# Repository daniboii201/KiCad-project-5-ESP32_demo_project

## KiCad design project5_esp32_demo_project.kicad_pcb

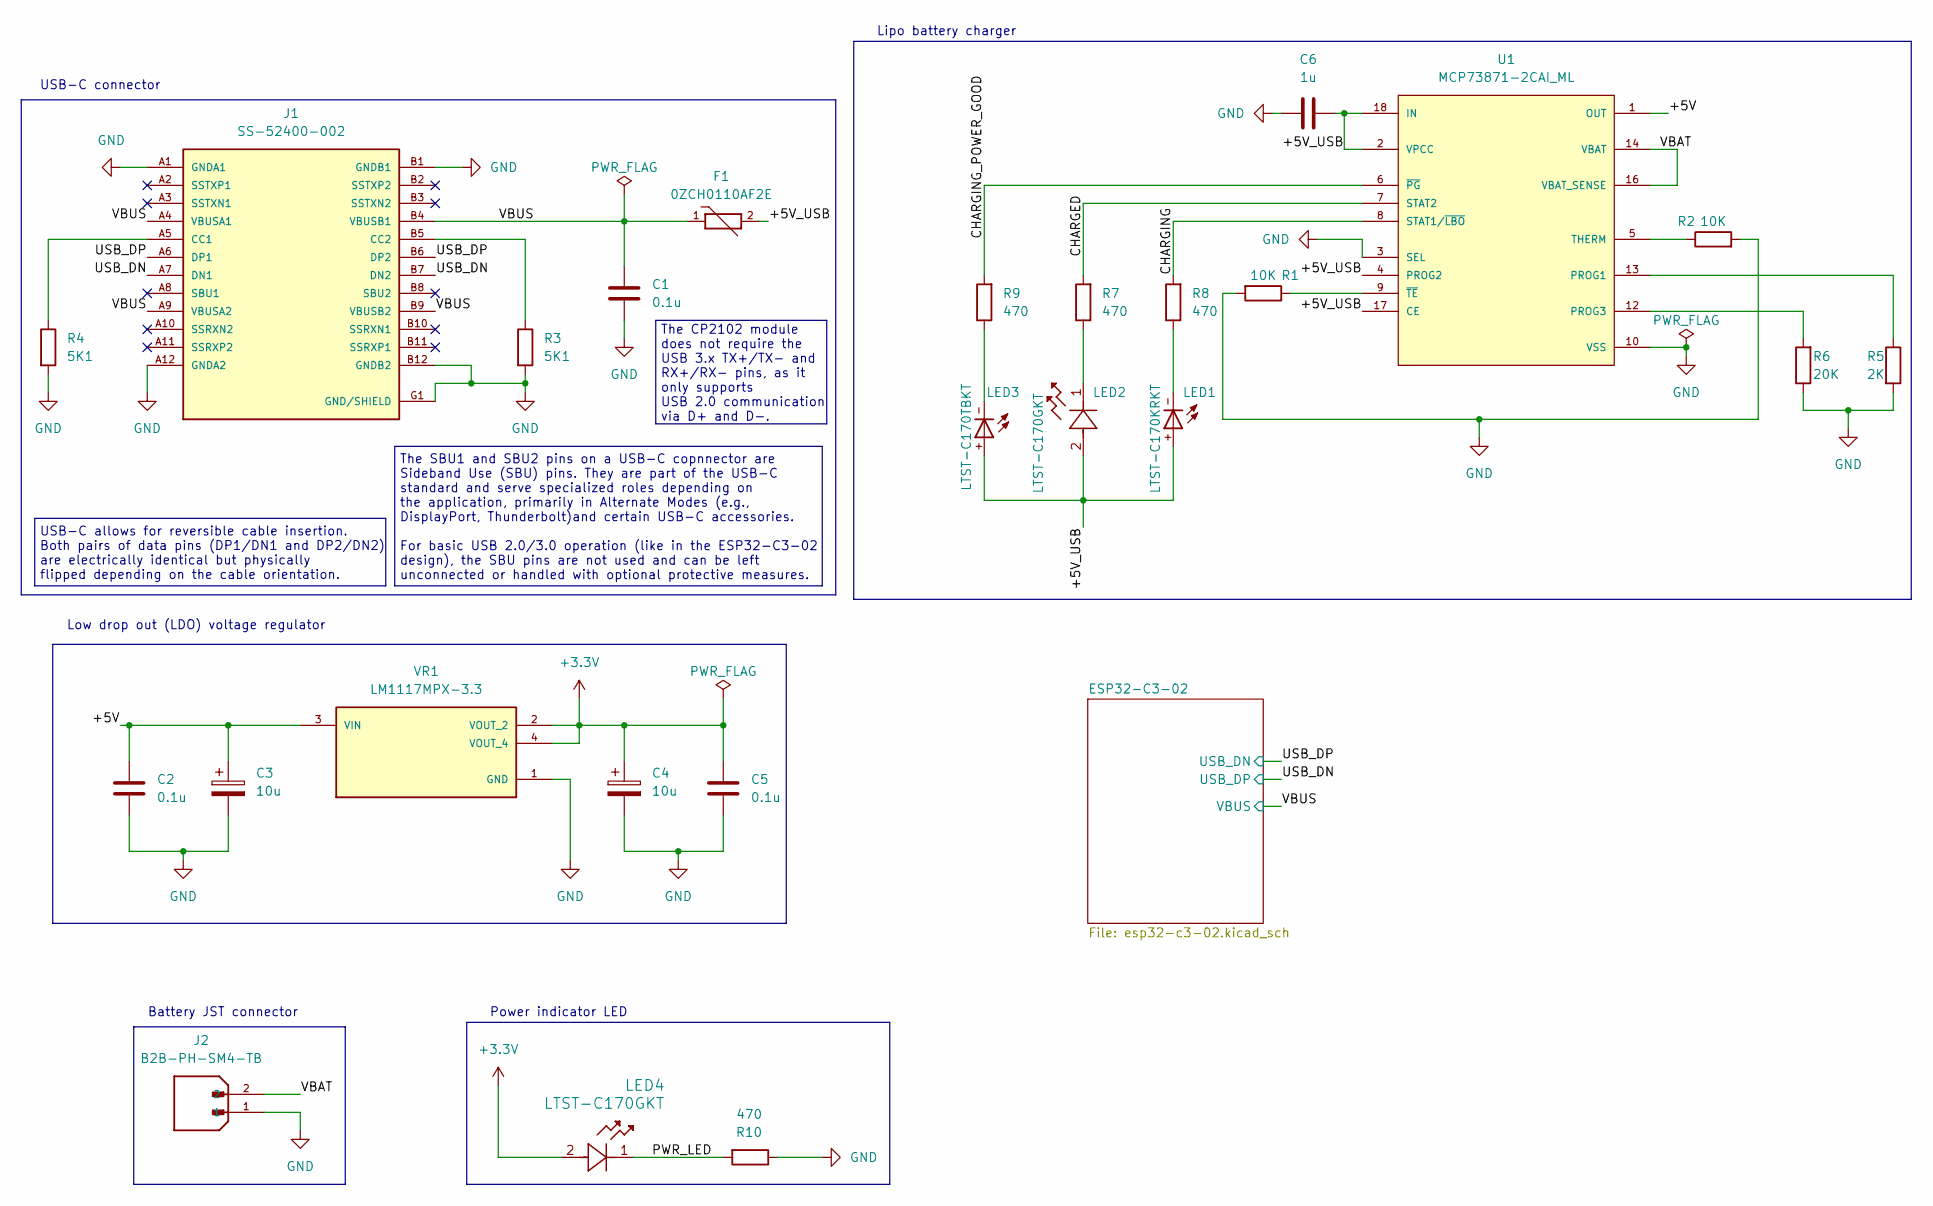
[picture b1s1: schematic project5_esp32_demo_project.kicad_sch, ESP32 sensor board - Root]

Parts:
C1, C2, C5: 0.1u; C_0805_2012Metric
C3, C4: 10u; T491A106K010AT7280
C6: 1u; C_0805_2012Metric
F1: 0ZCH0110AF2E; PARTREV Apr2023
J1: SS-52400-002; PARTREV A0
J2: B2B-PH-SM4-TB; PARTREV N/A
LED1: LTST-C170KRKT
LED2, LED4: LTST-C170GKT
LED3: LTST-C170TBKT
R1, R2: 10K; R_0805_2012Metric
R3, R4: 5K1; R_0805_2012Metric
R5: 2K; R_0805_2012Metric
R6: 20K; R_0805_2012Metric
R7, R8, R9, R10: 470; R_0805_2012Metric
U1: MCP73871-2CAI_ML; PARTREV D
VR1: LM1117MPX-3.3; PARTREV O

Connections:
+3.3V: C4.1, C5.1, LED4.2, VR1.2 (VOUT_2), VR1.4 (VOUT_4); also elsewhere on the board
/+5V: C2.1, C3.1, U1.1 (OUT), U1.20 (OUT), VR1.3 (VIN)
/+5V_USB: C6.2, F1.2, LED1.+, LED2.2, LED3.+, U1.2 (VPCC), U1.4 (PROG2), U1.17 (CE), U1.18 (IN), U1.19 (IN)
/CHARGED: R7.2, U1.7 (STAT2)
/CHARGING: R8.2, U1.8 (STAT1/~LBO)
/CHARGING_POWER_GOOD: R9.2, U1.6 (~PG)
/PWR_LED: LED4.1, R10.2
/USB_DN: J1.A7 (DN1), J1.B7 (DN2); also elsewhere on the board
/USB_DP: J1.A6 (DP1), J1.B6 (DP2); also elsewhere on the board
/VBAT: J2.2, U1.14 (VBAT), U1.15 (VBAT), U1.16 (VBAT_SENSE)
/VBUS: C1.1, F1.1, J1.A4 (VBUSA1), J1.A9 (VBUSA2), J1.B4 (VBUSB1), J1.B9 (VBUSB2); also elsewhere on the board
unnamed: J1.A5 (CC1), R4.1
unnamed: J1.B5 (CC2), R3.1
unnamed: LED1.-, R8.1
unnamed: LED2.1, R7.1
unnamed: LED3.-, R9.1
unnamed: R5.1, U1.13 (PROG1)
unnamed: R6.2, U1.12 (PROG3)
unnamed: R2.1, U1.5 (THERM)
unnamed: R1.1, U1.9 (~TE)

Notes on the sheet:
Battery JST connector
Lipo battery charger
The CP2102 module does not require the USB 3.x TX+/TX- and RX+/RX- pins, as it only supports USB 2.0 communication via D+ and D-.
Low drop out (LDO) voltage regulator
The SBU1 and SBU2 pins on a USB-C copnnector are Sideband Use (SBU) pins. They are part of the USB-C standard and serve specialized roles depending on the application, primarily in Alternate Modes (e.g., DisplayPort, Thunderbolt)and certain USB-C accessories. For basic USB 2.0/3.0 operation (like i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
USB-C connector
Power indicator LED
USB-C allows for reversible cable insertion. Both pairs of data pins (DP1/DN1 and DP2/DN2) are electrically identical but physically flipped depending on the cable orientation.

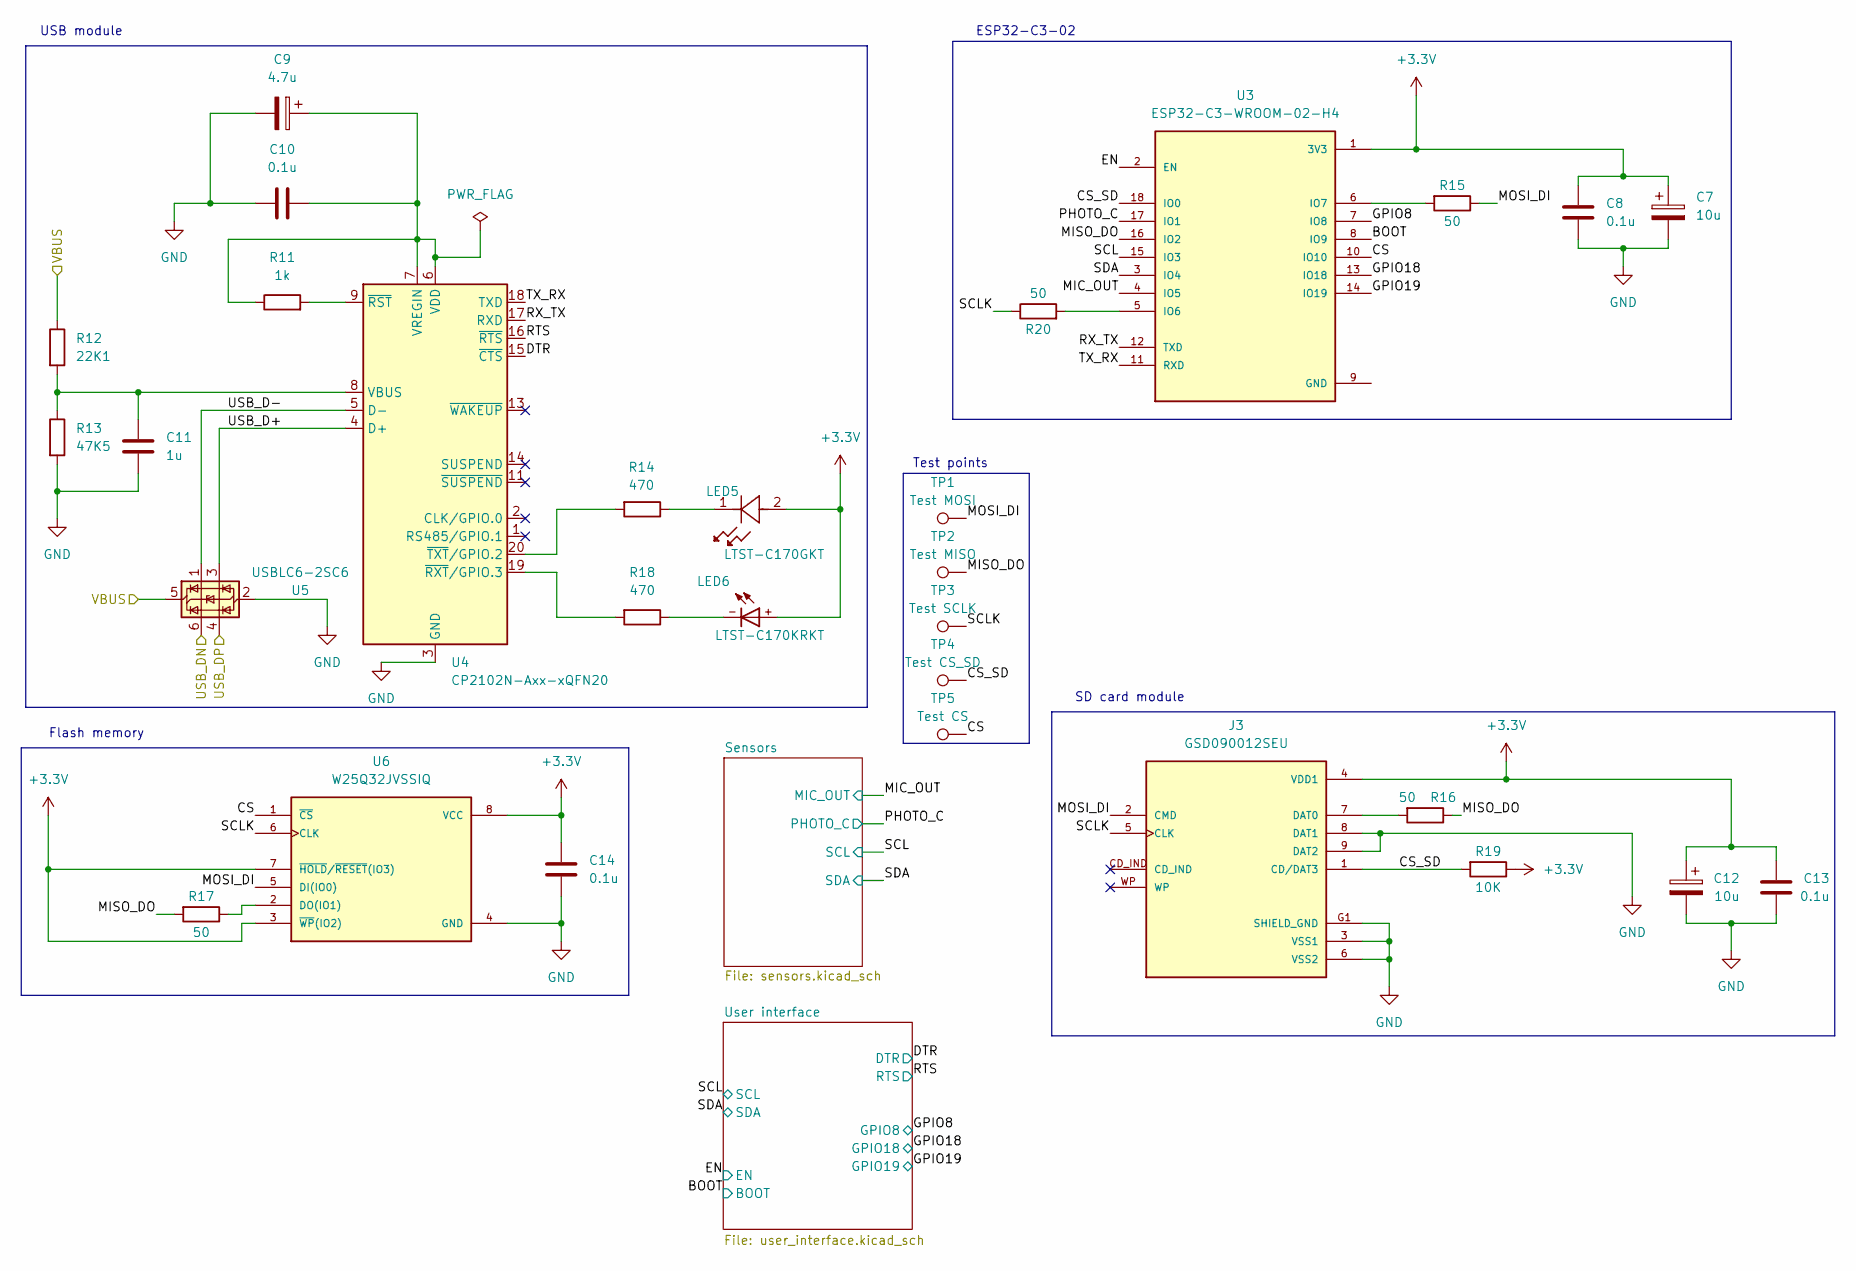
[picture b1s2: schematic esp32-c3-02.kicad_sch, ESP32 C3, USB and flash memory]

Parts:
C7, C12: 10u; T491A106K010AT7280
C8, C10, C13, C14: 0.1u; C_0805_2012Metric
C9: 4.7u; T491A106K010AT7280
C11: 1u; C_0805_2012Metric
J3: GSD090012SEU; PARTREV E
LED5: LTST-C170GKT
LED6: LTST-C170KRKT
R11: 1k; R_0805_2012Metric
R12: 22K1; R_0805_2012Metric
R13: 47K5; R_0805_2012Metric
R14, R18: 470; R_0805_2012Metric
R15, R16, R17, R20: 50; R_0805_2012Metric
R19: 10K; R_0805_2012Metric
TP1: Test MOSI; TestPoint_Pad_D1.0mm
TP2: Test MISO; TestPoint_Pad_D1.0mm
TP3: Test SCLK; TestPoint_Pad_D1.0mm
TP4: Test CS_SD; TestPoint_Pad_D1.0mm
TP5: Test CS; TestPoint_Pad_D1.0mm
U3: ESP32-C3-WROOM-02-H4
U4: CP2102N-Axx-xQFN20; QFN20_CP2102N_SIL
U5: USBLC6-2SC6; SOT-23-6
U6: W25Q32JVSSIQ; M_PART_NUMBER W25QXX

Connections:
+3.3V: C7.1, C8.1, C12.1, C13.1, C14.1, J3.4 (VDD1), LED5.2, LED6.+, R19.1, U3.1 (3V3), U6.3 (~WP(IO2)), U6.7 (~HOLD/~RESET(IO3)), U6.8 (VCC); also elsewhere on the board
/ESP32-C3-02/BOOT: U3.8 (IO9); also elsewhere on the board
/ESP32-C3-02/CS: TP5.1, U3.10 (IO10), U6.1 (~CS)
/ESP32-C3-02/CS_SD: J3.1 (CD/DAT3), R19.2, TP4.1, U3.18 (IO0)
/ESP32-C3-02/DTR: U4.15 (~CTS); also elsewhere on the board
/ESP32-C3-02/EN: U3.2 (EN); also elsewhere on the board
/ESP32-C3-02/GPIO8: U3.7 (IO8); also elsewhere on the board
/ESP32-C3-02/GPIO18: U3.13 (IO18); also elsewhere on the board
/ESP32-C3-02/GPIO19: U3.14 (IO19); also elsewhere on the board
/ESP32-C3-02/MIC_OUT: U3.4 (IO5); also elsewhere on the board
/ESP32-C3-02/MISO_DO: R16.1, R17.2, TP2.1, U3.16 (IO2)
/ESP32-C3-02/MOSI_DI: J3.2 (CMD), R15.1, TP1.1, U6.5 (DI(IO0))
/ESP32-C3-02/PHOTO_C: U3.17 (IO1); also elsewhere on the board
/ESP32-C3-02/RTS: U4.16 (~RTS); also elsewhere on the board
/ESP32-C3-02/RX_TX: U3.12 (TXD), U4.17 (RXD)
/ESP32-C3-02/SCL: U3.15 (IO3); also elsewhere on the board
/ESP32-C3-02/SCLK: J3.5 (CLK), R20.1, TP3.1, U6.6 (CLK)
/ESP32-C3-02/SDA: U3.3 (IO4); also elsewhere on the board
/ESP32-C3-02/TX_RX: U3.11 (RXD), U4.18 (TXD)
/ESP32-C3-02/USB_D+: U4.4 (D+), U5.3 (I/O2)
/ESP32-C3-02/USB_D-: U4.5 (D-), U5.1 (I/O1)
/USB_DN: U5.4 (I/O2); also elsewhere on the board
/USB_DP: U5.6 (I/O1); also elsewhere on the board
/VBUS: R12.1, U5.5 (VBUS); also elsewhere on the board
unnamed: J3.7 (DAT0), R16.2
unnamed: LED5.1, R14.1
unnamed: LED6.-, R18.1
unnamed: R20.2, U3.5 (IO6)
unnamed: R15.2, U3.6 (IO7)
unnamed: C11.1, R12.2, R13.1, U4.8 (VBUS)
unnamed: C9.1, C10.2, R11.1, U4.6 (VDD), U4.7 (VREGIN)
unnamed: R11.2, U4.9 (~RST)
unnamed: R18.2, U4.19 (~RXT/GPIO.3)
unnamed: R14.2, U4.20 (~TXT/GPIO.2)
unnamed: R17.1, U6.2 (DO(IO1))

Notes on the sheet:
ESP32-C3-02
Flash memory
SD card module
USB module
Test points

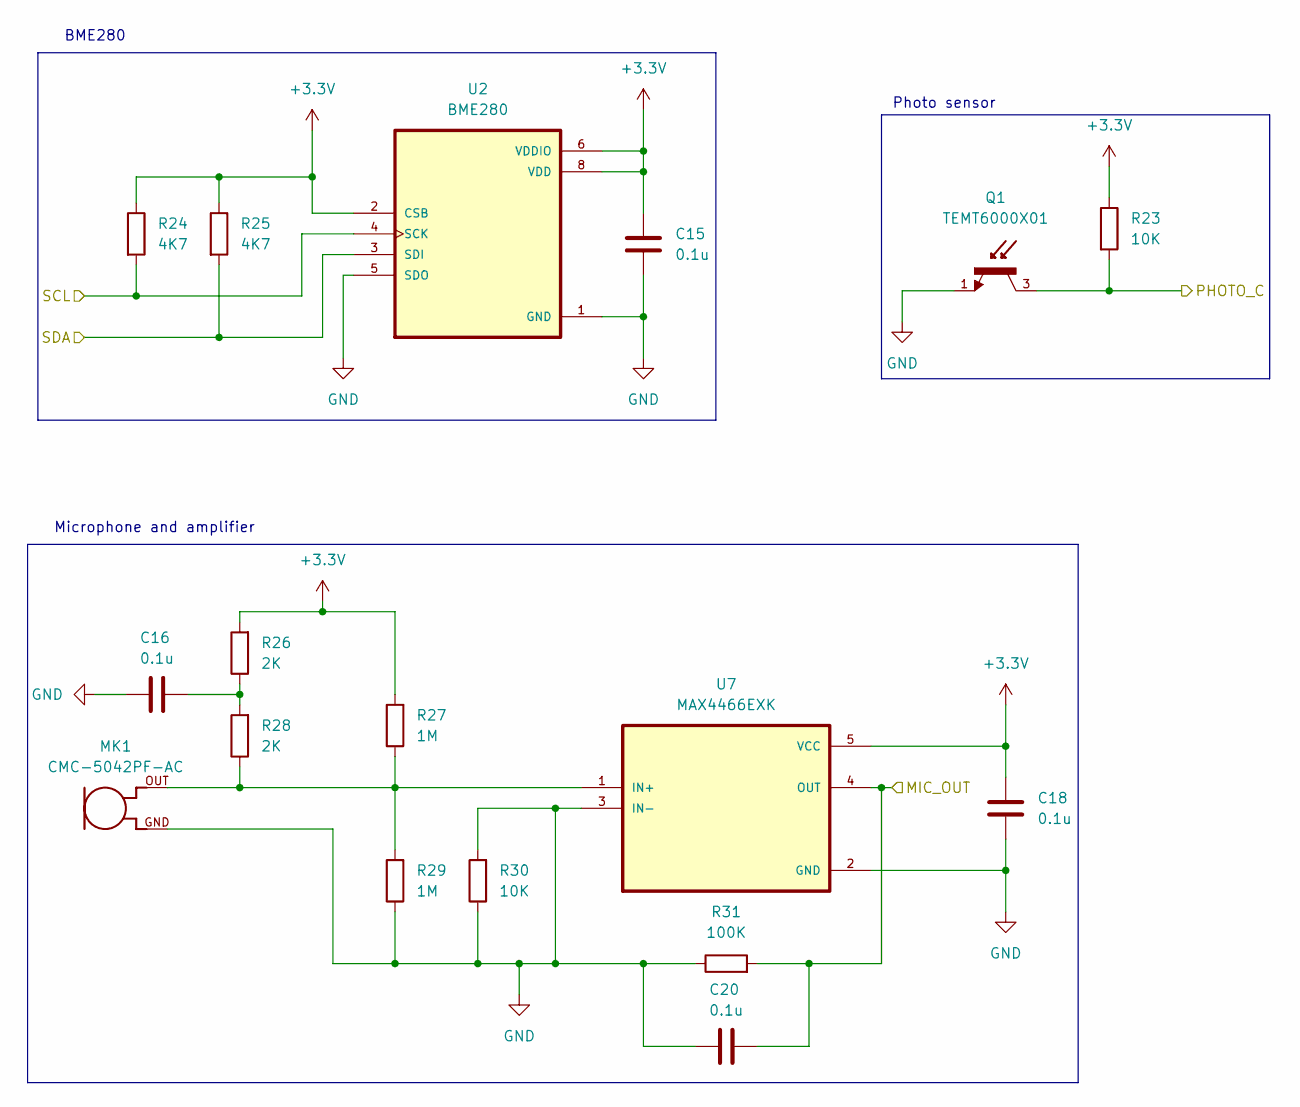
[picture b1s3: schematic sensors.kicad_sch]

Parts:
C15, C16, C18, C20: 0.1u; C_0805_2012Metric
MK1: CMC-5042PF-AC
Q1: TEMT6000X01; PARTREV 1.9
R23, R30: 10K; R_0805_2012Metric
R24, R25: 4K7; R_0805_2012Metric
R26, R28: 2K; R_0805_2012Metric
R27, R29: 1M; R_0805_2012Metric
R31: 100K; R_0805_2012Metric
U2: BME280
U7: MAX4466EXK

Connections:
+3.3V: C15.1, C18.1, R23.1, R24.1, R25.1, R26.2, R27.2, U2.2 (CSB), U2.6 (VDDIO), U2.8 (VDD), U7.5 (VCC); also elsewhere on the board
/ESP32-C3-02/MIC_OUT: C20.2, R31.2, U7.4 (OUT); also elsewhere on the board
/ESP32-C3-02/PHOTO_C: Q1.3, R23.2; also elsewhere on the board
/ESP32-C3-02/SCL: R24.2, U2.4 (SCK); also elsewhere on the board
/ESP32-C3-02/SDA: R25.2, U2.3 (SDI); also elsewhere on the board
unnamed: C16.2, R26.1, R28.2
unnamed: MK1.OUT, R27.1, R28.1, R29.2, U7.1 (IN+)

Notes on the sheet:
BME280
Microphone and amplifier
Photo sensor

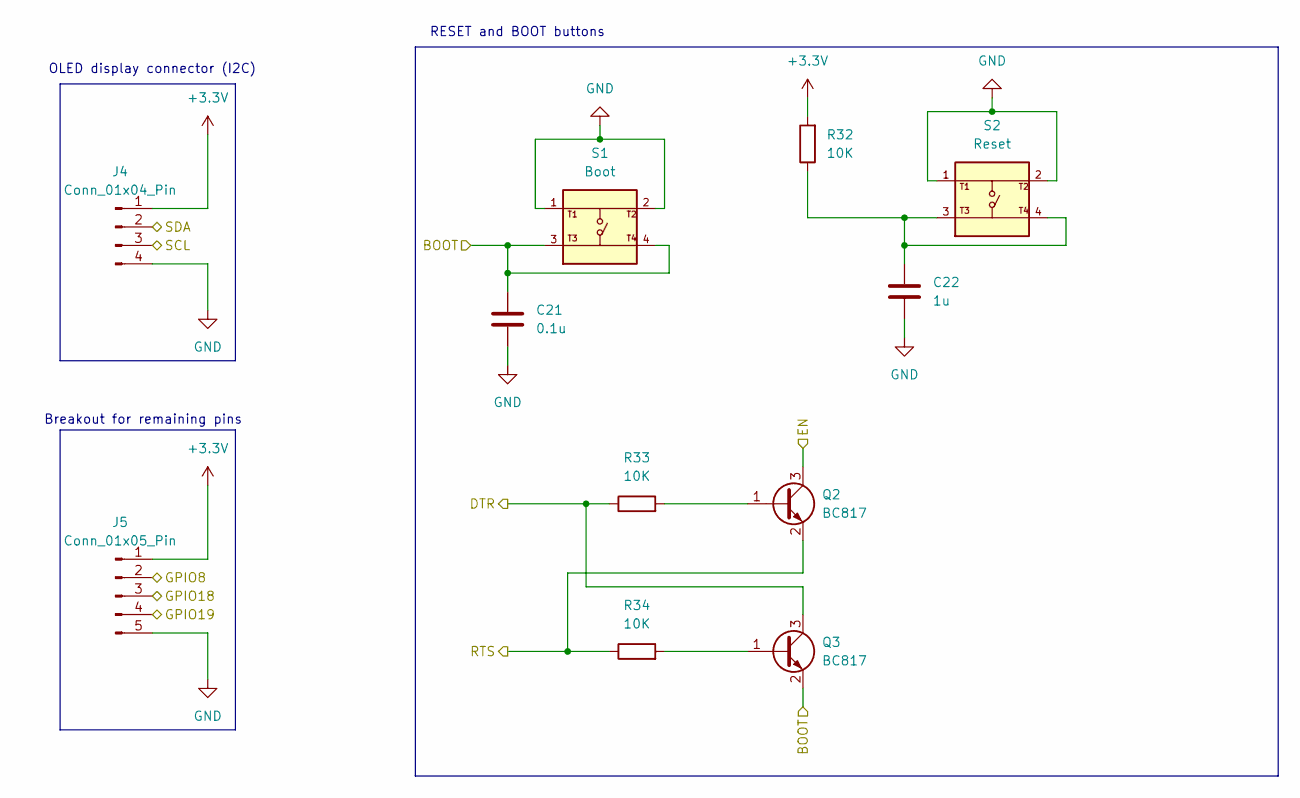
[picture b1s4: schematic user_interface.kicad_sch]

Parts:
C21: 0.1u; C_0805_2012Metric
C22: 1u; C_0805_2012Metric
J4: Conn_01x04_Pin; PinHeader_1x04_P2.54mm_Vertical
J5: Conn_01x05_Pin; PinHeader_1x05_P2.54mm_Vertical
Q2, Q3: BC817; SOT-23
R32, R33, R34: 10K; R_0805_2012Metric
S1: Boot; USLPT2819DT2TR; PARTREV P
S2: Reset; USLPT2819DT2TR; PARTREV P

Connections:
+3.3V: J4.1, J5.1, R32.2; also elsewhere on the board
/ESP32-C3-02/BOOT: C21.1, Q3.2 (E), S1.3, S1.4; also elsewhere on the board
/ESP32-C3-02/DTR: Q3.3 (C), R33.1; also elsewhere on the board
/ESP32-C3-02/EN: Q2.3 (C); also elsewhere on the board
/ESP32-C3-02/GPIO8: J5.2; also elsewhere on the board
/ESP32-C3-02/GPIO18: J5.3; also elsewhere on the board
/ESP32-C3-02/GPIO19: J5.4; also elsewhere on the board
/ESP32-C3-02/RTS: Q2.2 (E), R34.1; also elsewhere on the board
/ESP32-C3-02/SCL: J4.3; also elsewhere on the board
/ESP32-C3-02/SDA: J4.2; also elsewhere on the board
unnamed: C22.1, R32.1, S2.3, S2.4
unnamed: Q2.1 (B), R33.2
unnamed: Q3.1 (B), R34.2

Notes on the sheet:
RESET and BOOT buttons
OLED display connector (I2C)
Breakout for remaining pins

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
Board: 4 copper layers, 83 parts (0 on the bottom side), 57 nets, no tracks yet.

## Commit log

2026-01-14 1.1.1 Starting with schematic design
2026-01-14 1.1.2 Lipo battery charger
2026-01-19 1.1.3 Design USB port subcircuit
2026-01-19 1.1.4 Create the first few nets
2026-01-19 1.1.5 Finish the design for the LiPo charger
2026-01-19 1.1.6 Design the voltage regulator subcircuit
2026-01-19 1.1.7 Design the battery connector subcircuit
2026-01-19 1.1.8 Add a hierarchical sheet symbol to page 2
2026-01-19 1.1.9 Finish work in sheet 1
2026-01-19 1.2.0 Schematic design page 2
2026-01-19 1.2.1 Design the USB to UART bridge subcircuit
2026-01-19 1.2.2 Project Design the ESP32 module subcircuit
2026-01-19 1.2.3 Design the SD card module subcircuit
2026-01-19 1.2.4 Design the flash memory subcircuit
2026-01-20 1.2.5 Create hierarchical sheet 3 & 4 symbols
2026-01-20 1.2.6 Add test points
2026-01-20 1.2.7 Schematic design sheet #3: Sensors
2026-01-20 1.2.8 Design the BME280 subcircuit
2026-01-20 1.2.9 Design the ambient light sensor subcircuit
2026-01-20 1.3.0 Design the sound sensor subcircuit
2026-01-21 1.3.1 Schematic design sheet #4: User interface
2026-01-21 1.3.2 Wiring of the EN and BOOT buttons
2026-01-22 1.3.3 Symbol and footprint associations
2026-01-22 1.3.4 Electrical Rules Check
2026-01-30 1.3.5 Layout editor setup
2026-01-30 1.3.6 Netclass setup
2026-01-30 1.3.7 Import schematic into the layout editor
2026-01-30 1.3.9 Bring remaining components to the layout editor
2026-02-03 1.4.0 Main components placement
2026-02-03 1.4.1 Placement of subcircuits
2026-02-03 1.4.2 Components placement v2
2026-02-03 1.4.3 Draw the edge cut (rough board outline)
